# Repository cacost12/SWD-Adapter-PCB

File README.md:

# A0004-SWD-Adapter
20 pin adapter board for programming L0005 using a J-Link

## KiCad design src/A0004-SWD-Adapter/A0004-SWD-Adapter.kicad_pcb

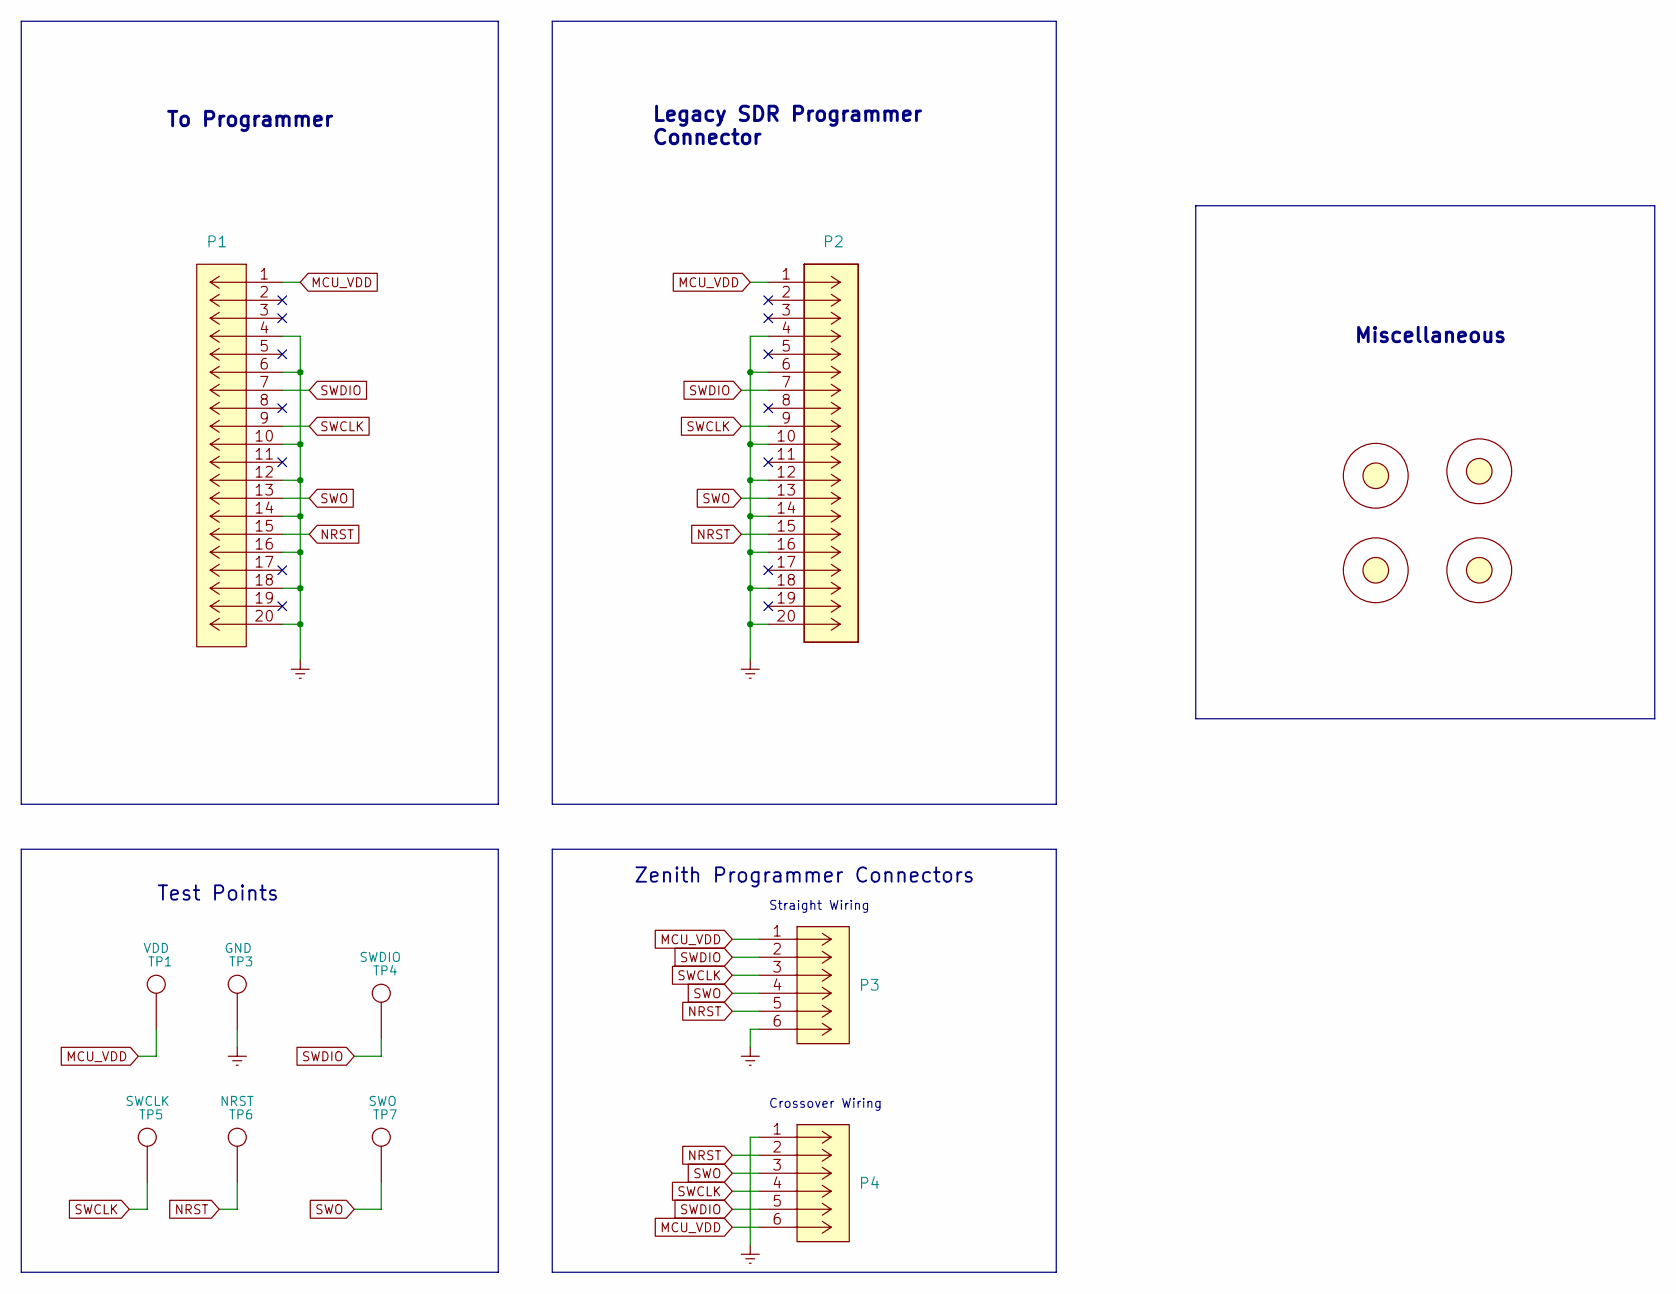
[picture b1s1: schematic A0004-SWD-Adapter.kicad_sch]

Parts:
H1, H2, H3, H4: Mounting-Hole; MountingHole_4.3mm_M4_DIN965
P1: LARGE_SBH11-PBPC-D10-RA-BK_1; LARGE_SBH11-PBPC-D10-RA-BK
P2: SMALL_3220-20-0200-00
P3, P4: 0530470610; 53047-0610
TP1: VDD; TP
TP3: GND; TP
TP4: SWDIO; TP
TP5: SWCLK; TP
TP6: NRST; TP
TP7: SWO; TP

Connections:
Earth: P1.4, P1.6, P1.10, P1.12, P1.14, P1.16, P1.18, P1.20, P2.4, P2.6, P2.10, P2.12, P2.14, P2.16, P2.18, P2.20, P3.6, P4.1, TP3.1
MCU_VDD: P1.1, P2.1, P3.1, P4.6, TP1.1
NRST: P1.15, P2.15, P3.5, P4.2, TP6.1
SWCLK: P1.9, P2.9, P3.3, P4.4, TP5.1
SWDIO: P1.7, P2.7, P3.2, P4.5, TP4.1
SWO: P1.13, P2.13, P3.4, P4.3, TP7.1

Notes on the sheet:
Zenith Programmer Connectors
Straight Wiring
Miscellaneous
Legacy SDR Programmer Connector
Test Points
Crossover Wiring
To Programmer

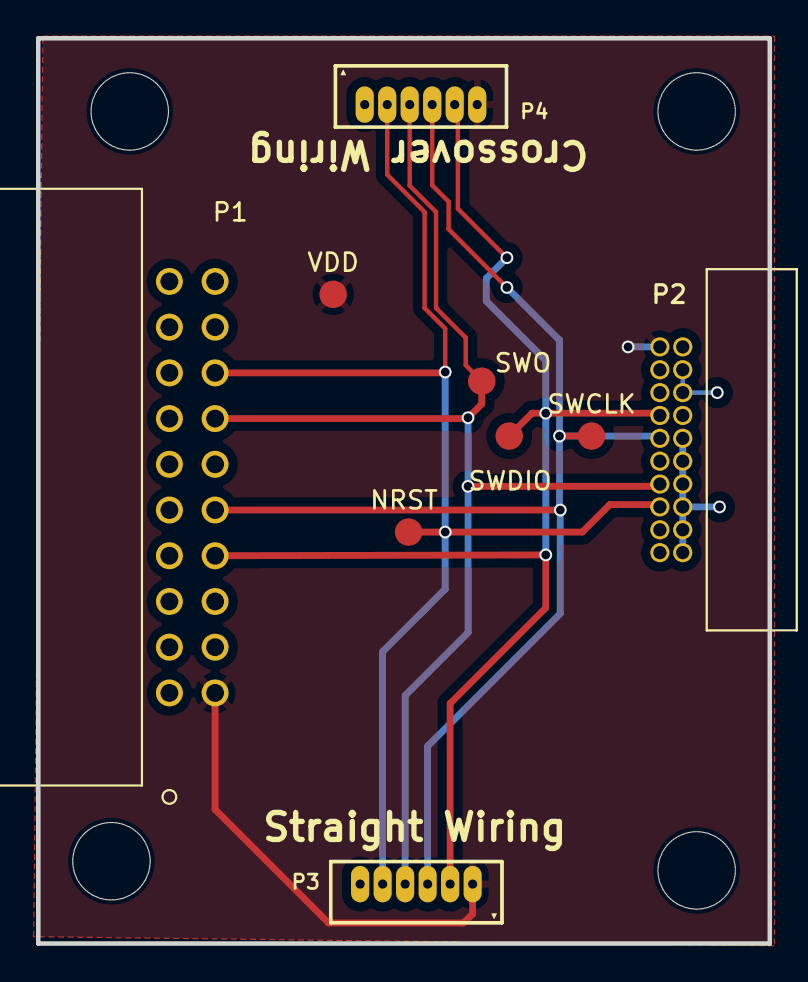
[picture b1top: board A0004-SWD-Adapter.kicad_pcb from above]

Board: 2 copper layers, 40.6 x 50.3 mm, 14 parts (1 on the bottom side), 6 nets.

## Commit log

2022-12-24 copied files over from old repository
2023-08-03 added new programming connector to lib files
2023-08-03 implemented schematic with new zenith programmer connectors
2023-08-03 routed board with new programmer connectors
2023-08-03 resolved layout DRC errors and generated fabrication outputs
